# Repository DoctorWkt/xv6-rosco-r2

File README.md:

# xv6-rosco-r2 - xv6 on the Rosco m68k Classic v2

This project aims to port the [xv6](https://github.com/mit-pdos/xv6-public) kernel
to the [Rosco m68k Classic v2](https://github.com/rosco-m68k/rosco_m68k) SBC. The
goal is to have a Unix-like kernel with a BSD userland on top of it, much like my
previous [xv6-freebsd](https://github.com/DoctorWkt/xv6-freebsd) project.

This time, I'm going to do things in a few stages:

 - Stage 1: Bring up a system with just one program running at a time. I've
   done this before with the [Nine-E](https://github.com/DoctorWkt/Nine-E/) project.
 - Stage 2: Move to multiple processes but with no process pre-emption. I've done
   this before with the [MMU09](https://github.com/DoctorWkt/MMU09) project.
 - Stage 3: Enable process pre-emption and then slowly add in all the libraries
   and userland from the [xv6-freebsd](https://github.com/DoctorWkt/xv6-freebsd) project.

Please note: this is a work in progress. It's definitely not a finished and polished
system at the moment. You will have to figure some things out yourself.

## Hardware Options

I'm finding the bit-bang SD card very slow. I also really don't want to have to put
in a relocating loader into the kernel. So I have designed an
[expansion board](hardware) with 1M of RAM and a
[CH375](https://www.electrodragon.com/product/ch375-module-reading-and-writing-u-diskusb-communicate/)
USB interface. It has a
[base register](https://en.wikipedia.org/wiki/Base_and_bounds) in front of the RAM, so that I can have multiple processes, but each one will think that they start at the same base address.

There are two Git branches for this project:

 - This branch, `ch375`, has the code that supports the above expansion board.
   In this version, the system has multiple processes running at any time.
 - The `main` branch has the code that supports the SD card. In that version,
   there is only one program running at any time.

## Running the System in an Emulator

If you want to try this out without the hardware, then build my
[r68k emulator](https://github.com/DoctorWkt/rosco_m68k/tree/wkt_r68k/code/tools/r68k).

In this repository, I have provided a copy of the `xv6` kernel binary: `kern/xv6.bin`, and a filesystem image: `fs.img`. Copy these to where you built the emulator. Now you can do:

```
$ ./r68k -U fs.img xv6.bin
```

and you will see:

```
Welcome to xv6
About to initialise the CH375
xv6 superblock: size 9000 nblocks 8949 ninodes 200
  nlog 20 logstart 2 inodestart 22 bmap start 48
$ ls -l
-rwxrwxrwx     1 root root     46 Wed Sep  4 23:49:10 README
drwxrwxrwx     1 root root    896 Mon Oct 14 21:38:24 bin
drwxrwxrwx     1 root root     64 Wed Sep  4 23:27:09 etc
-rwxrwxrwx     1 root root   6071 Tue Aug  8 01:30:40 roff_manual
$
```

## Building the System for the CH375 Device

I need to put more docs here, but for now ...

You will need the [rosco toolchain](https://rosco-m68k.com/docs/toolchain-installation)
installed on your system as well as `mtools` and `mkfs.vfat`. There are probably a few
more things needed - let me know what I've forgotten.

At the top level, do a `make` to build the kernel, the tools, the libraries and
the commands. This will build the `fs.img` xv6 filesystem image.

Yes, there are a heap of warnings. Over time, I will try to fix them.

Then, do a `make sdcard.img`. This creates the SD card image with a bootable copy
of the `xv6` kernel.

Now write `sdcard.img` to your SD card, write `fs.img` to your USB key, put each
in the correct socket, and boot your rosco board with the CH375 expansion board.

You should see something like:

```
                                 ___ ___ _   
 ___ ___ ___ ___ ___       _____|  _| . | |_ 
|  _| . |_ -|  _| . |     |     | . | . | '_|
|_| |___|___|___|___|_____|_|_|_|___|___|_,_|
                    |_____|      Classic 2.42

MC68010 CPU @ 10.0MHz with 14680064 bytes RAM
Initializing hard drives... No IDE interface found
Searching for boot media...
SD v2 card:
  Partition 1: Loading "/ROSCODE1.BIN"....
Loaded 16600 bytes in ~1 sec.

Welcome to xv6
About to initialise the CH375
xv6 superblock: size 9000 nblocks 8949 ninodes 200
  nlog 20 logstart 2 inodestart 22 bmap start 48
$ setdate
Enter new date (yyyy-mm-dd): 2024-10-14
Enter new time (hh:mm:ss): 11:07:00
New time is Mon Oct 14 11:07:00 2024

$ touch README
$ ls -l
-rwxrwxrwx     1 root root     46 Mon Oct 14 11:07:05 README
-rwxrwxrwx     1 root root  42497 Thu Jan  1 00:01:13 bar
drwxrwxrwx     1 root root    896 Mon Oct 14 00:49:48 bin
drwxrwxrwx     1 root root     64 Wed Sep  4 23:27:09 etc
-rwxrwxrwx     1 root root  42497 Thu Jan  1 00:00:43 foo
-rwxrwxrwx     1 root root   6071 Tue Aug  8 01:30:40 roff_manual
$
```

## Status -- 29 Oct 2024

I've decided to replace the BSD libraries and commands with
the libraries and commands from Minix. There are now a lot 
more commands, and the libraries are smaller too.

## Status -- 22 Oct 2024

I've added double-indirect blocks to the filesystem. Files can
now be up to 32 Megabytes in size.

## Status - 21 Oct 2024

I've imported some assembly language versions of `memmove()` and `memset()`.
I've also rewritten some of the loops in the `balloc()` block allocation
function. All of this has greatly improved the file I/O speed, especially
writes to disk.

## Status - 17 Oct 2024

I found a workaround for the problem with the `vi` editor writing files really
slowly, but I haven't found the underlying bug yet.

**BIG CHANGE**: I modified the disk block buffer to _not_ write out dirty blocks,
and added the `sync` program and `sync()` system call to flush out dirty blocks.
This improves disk performance, but you must remember to `sync` before turning off
the system now!

## Status - 15 Oct 2024

The PCBs have arrived and the CH375 device works fine. While waiting for the PCBs,
I got `fork()`, `exit()` and `wait()` working correctly in the emulator. They also
work in hardware with the memory on the PCB.

There is now an `init` process, and I've imported the `xv6` shell. So now the system
has working processes. Pipes are also working, so you can now do:

```
$ roff roff_manual | less
```

## Status - 5 Oct 2024

I have started the work in the `ch375` branch to add processes to the system.
There is still only one process, but I've brought back the `proc` structure
and I've begun the work to write the memory management code.

## Status - 1 Oct 2024

I've imported the KiCad design for my expansion RAM + base register + CH375 board
and done a bit of documentation on it. I've ordered PCBs and I'm waiting for them
to arrive so I can test if the board works.

## Status - 24 Sept 2024

I've imported a bunch more commands, this time from FUZIX.
I also got the kernel to return an `errno` value back to
userland.

## Status - 19 Sept 2024

I've imported more programs, replaced `malloc()` with the Minix version and
added `readline()` support to the shell.

## Status - 17 Sept 2024

I have stage 1 up and running on the
[Rosco m68k Classic v2](https://github.com/rosco-m68k/rosco_m68k) SBC with the
bit-bang SD card. There are only a few programs in the userland at present:
`cal`, `cat`, `echo`, `ls`, `rm`, `sh`.

The kernel has these system calls:
`exit()`, `read()`, `write()`, `open()`, `close()`, `link()`, `unlink()`, `chdir()`,
`fstat()`, `dup()`, `mkdir()`, `spawn()`, `lseek()`, `time()`, `ioctl()`.

As there are no processes, `spawn()` acts like the Unix `exec()` and replaces the
current program, and `exit()` simply `spawn()s` the shell.

The next steps are to port more programs over from
[xv6-freebsd](https://github.com/DoctorWkt/xv6-freebsd) and
[Nine-E](https://github.com/DoctorWkt/Nine-E/).

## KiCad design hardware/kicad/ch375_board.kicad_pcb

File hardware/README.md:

## RAM Expansion and CH375 Board for Rosco Classic v2

The 680000 doesn't have any built-in memory management, and I didn't want
to write the code to load and relocate an ELF binary so that it could run
at any specific base memory address. I also wanted to support the
[CH375](https://www.electrodragon.com/product/ch375-module-reading-and-writing-u-diskusb-communicate/)
device, which provides an 8-bit parallel interface to USB block devices.

Thus, I have built an expansion card that `xv6` uses. It has two main
components:

 - the CH375 device and associated addressing/interrupt components
 - 1M of expansion RAM along with primitive memory management hardware

In this directory you can find the [KiCad board design](kicad), the
[code](pld) for the two GALs on the board, a PDF of the
[schematic](schematic.pdf), a mock-up [image](ch375_board.jpg)
of the board and some [documentation](docs) on the CH375 device.

## The CH375 Device

The CH375 provides block-level access to a USB via an 8-bit TTL-compatible
parallel interface. We need to decode two I/O addresses for this device.
We also need to convert the active-low interrupt that the CH375 generates
into several lines that make it compatible with the 68000 auto-vector
interrupt protocol.

The [GAL code](pld/ch375logic.pld) that interfaces between the 68000 and the
CH375 does these things:

 - It sets the CH375 chip select low for addresses $00FFF001 (data) and
   $00FFF003 (commands), and lowers DTACK at the same time.
 - After the CH375 sends an interrupt, the CPU responds with various lines
   to acknowledge the interrupt. The GAL determines when to drop VPA to
   let the CPU know that the interrupt has been acknowledged.

## The Expansion RAM and the Base Register

The expansion board adds 1M of expansion RAM to the Rosco classic r2 board.
It also provides primitive memory management hardware in the form of a
[base register](https://en.wikipedia.org/wiki/Base_and_bounds). Let's look
at how this works.

The base register is a 4-bit I/O register (initially zero) which can be written
to at address $00FFE001.

The base register's value, multiplied by 64K, is then added to any expansion
RAM address. This allows the "base" of the expansion RAM to be positioned
at any of sixteen 64K-spaced locations.

For example, with the base register set to 0x0, expansion memory address
$00100124 becomes $00100124 + $0000000 => $00100124. But if the base
register was set to 0x4, then address $00100124 becomes
$00100124 + $0040000 => $00140124.

The purpose of the base register is to allow an operating system to load
multiple programs into the expansion RAM, each starting at a different
64K position. By setting the base register suitably, each program will
think that it starts at $00100000 instead of its actual physical location.

In terms of hardware, the register itself is a 74HCT161 4-bit register, and the
[GAL code](pld/ramdecode.pld) in the second GAL decodes its $00FFE001 address.
This is connected to a 74HCT283 4-bit adder. The base register's value is added
to address lines A16...A19 to form the physical address that is then sent to the
two RAM chips.

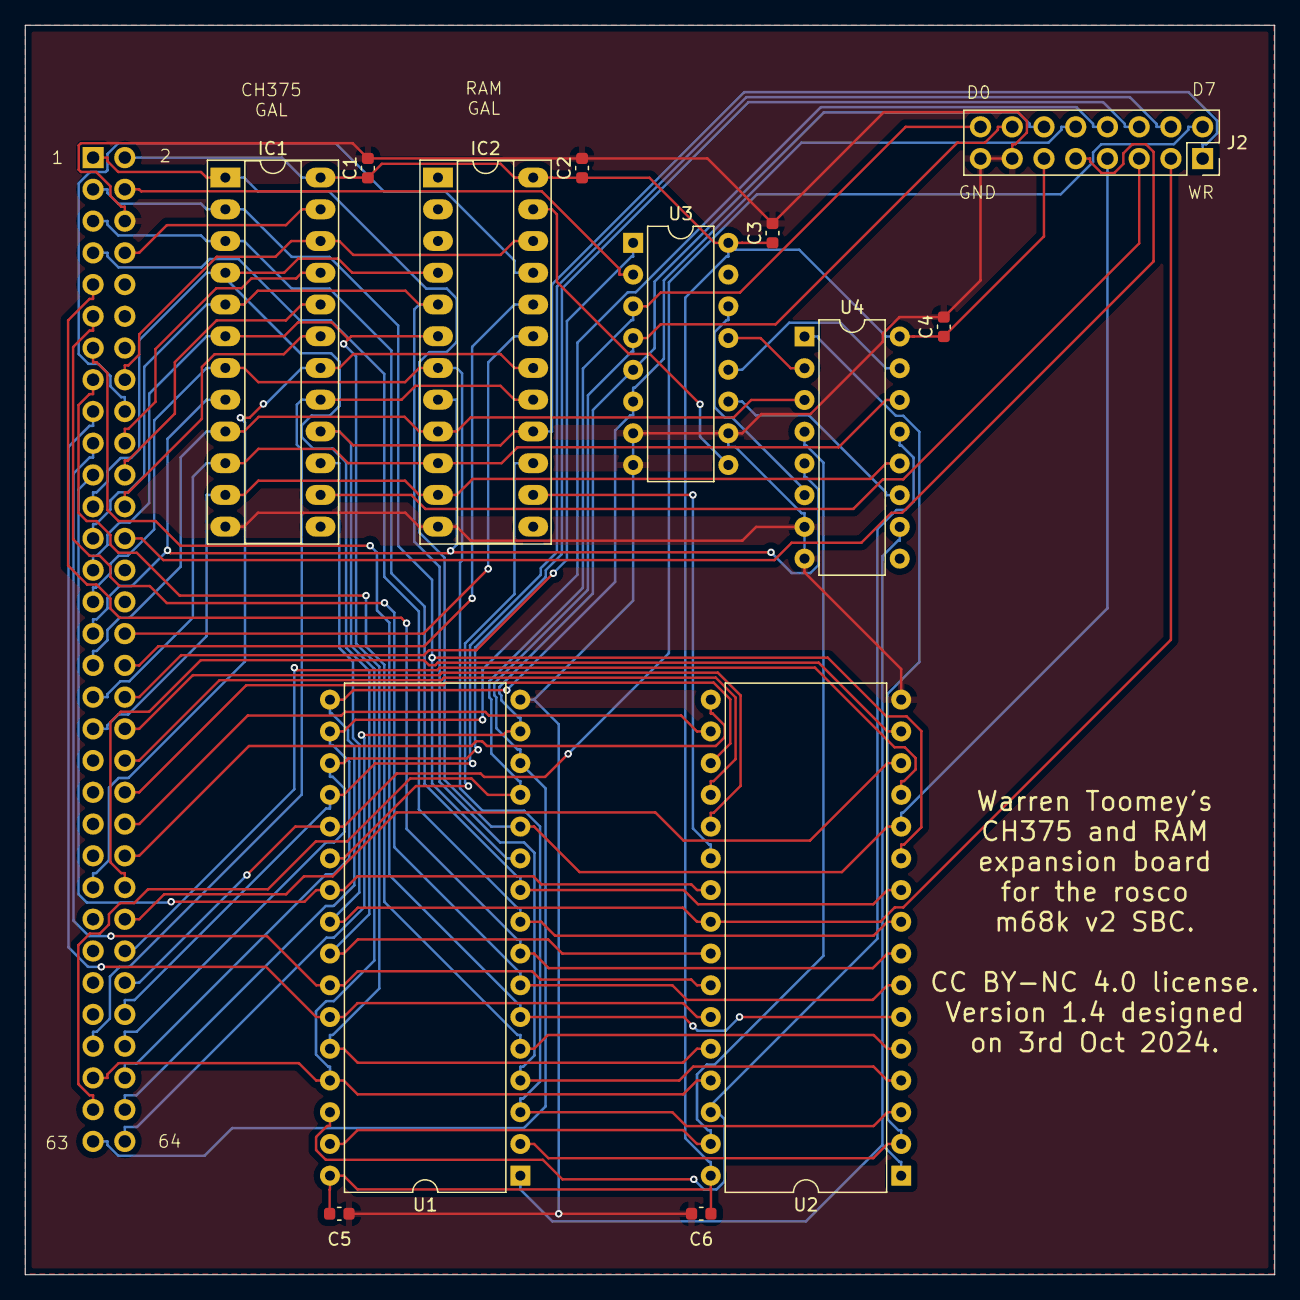
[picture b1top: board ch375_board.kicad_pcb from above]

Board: 2 copper layers, 100.0 x 100.0 mm, 14 parts (1 on the bottom side), 64 nets.

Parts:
C1, C2, C3, C4, C5, C6: 100nF; C_0603_1608Metric
IC1, IC2: ATF22V10C; DIP-24_W7.62mm_Socket_LongPads
J1: Conn_02x32_Odd_Even; PinSocket_2x32_P2.54mm_Vertical
J2: Conn_02x08_Odd_Even; PinSocket_2x08_P2.54mm_Vertical
U1, U2: AS6C4008-55PCN; DIP-32_W15.24mm
U3: 74HCT161; DIP-16_W7.62mm
U4: 74LS283; DIP-16_W7.62mm

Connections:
A1: IC1.1 (I1/CLK), J1.1, J2.7, U1.12 (A0), U2.12 (A0)
A2: IC1.2 (I2), J1.3, U1.11 (A1), U2.11 (A1)
A3: IC1.3 (I3), J1.5, U1.10 (A2), U2.10 (A2)
A4: J1.7, U1.9 (A3), U2.9 (A3)
A5: J1.9, U1.8 (A4), U2.8 (A4)
A6: J1.11, U1.7 (A5), U2.7 (A5)
A7: J1.13, U1.6 (A6), U2.6 (A6)
A8: J1.15, U1.5 (A7), U2.5 (A7)
A9: J1.17, U1.27 (A8), U2.27 (A8)
A10: J1.19, U1.26 (A9), U2.26 (A9)
A11: J1.21, U1.23 (A10), U2.23 (A10)
A12: IC1.4 (I4/PD), IC2.4 (I4/PD), J1.23, U1.25 (A11), U2.25 (A11)
A13: IC1.5 (I5), IC2.5 (I5), J1.25, U1.4 (A12), U2.4 (A12)
A14: IC1.6 (I6), IC2.6 (I6), J1.27, U1.28 (A13), U2.28 (A13)
A15: IC1.7 (I7), IC2.7 (I7), J1.29, U1.3 (A14), U2.3 (A14)
A16: IC1.8 (I8), IC2.8 (I8), J1.31, U4.5 (A1)
A17: IC1.9 (I9), IC2.9 (I9), J1.33, U4.3 (A2)
A18: IC1.10 (I10), IC2.10 (I10), J1.35, U4.14 (A3)
A19: IC1.11 (I11), IC2.11 (I11), J1.37, U4.12 (A4)
AS: IC1.18 (IO5), IC2.18 (IO5), J1.47
CLK: J1.4, U3.2 (CP)
D0: J1.61, J2.16, U1.13 (DQ0), U3.3 (D0)
D1: J1.63, J2.14, U1.14 (DQ1), U3.4 (D1)
D2: J1.64, J2.12, U1.15 (DQ2), U3.5 (D2)
D3: J1.62, J2.10, U1.17 (DQ3), U3.6 (D3)
D4: J1.60, J2.8, U1.18 (DQ4)
D5: J1.58, J2.6, U1.19 (DQ5)
D6: J1.56, J2.4, U1.20 (DQ6)
D7: J1.54, J2.2, U1.21 (DQ7)
D8: J1.52, U2.13 (DQ0)
D9: J1.50, U2.14 (DQ1)
D10: J1.48, U2.15 (DQ2)
D11: J1.46, U2.17 (DQ3)
D12: J1.44, U2.18 (DQ4)
D13: J1.42, U2.19 (DQ5)
D14: J1.40, U2.20 (DQ6)
D15: J1.38, U2.21 (DQ7)
DTACK: IC1.17 (I04), IC2.17 (I04), J1.57
EXPSEL: IC2.21 (IO8), J1.18
FC0: IC1.21 (IO8), J1.20
FC1: IC1.20 (IO7), J1.22
FC2: IC1.19 (IO6), J1.24
GND: C1.2, C2.2, C3.2, C4.2, C5.2, C6.2, IC1.12 (GND), IC2.12 (GND), J1.6, J2.13, J2.15, U1.16 (VSS), U2.16 (VSS), U3.7 (CEP), U3.8 (GND), U3.10 (CET), U4.7 (C0), U4.8 (GND)
IOSEL: IC1.22 (IO9), IC2.22 (IO9), J1.16
IRQ5: J1.26, J2.9
LDS: IC2.19 (IO6), J1.32
unnamed: U3.14 (Q0), U4.6 (B1)
unnamed: U3.13 (Q1), U4.2 (B2)
unnamed: U3.12 (Q2), U4.15 (B3)
unnamed: U3.11 (Q3), U4.11 (B4)
P16: U1.31 (A15), U2.31 (A15), U4.4 (S1)
P17: U1.2 (A16), U2.2 (A16), U4.1 (S2)
P18: U1.30 (A17), U2.30 (A17), U4.13 (S3)
P19: U1.1 (A18), U2.1 (A18), U4.10 (S4)
RESET: J1.36, U3.1 (~MR)
R~W: IC1.16 (IO3), IC2.16 (IO3), J1.59, J2.1, U1.29 (WE#), U2.29 (WE#)
UDS: IC2.20 (IO7), J1.34
VCC: C1.1, C2.1, C3.1, C4.1, C5.1, C6.1, IC1.24 (VCC), IC2.24 (VCC), J1.2, J2.11, U1.32 (VCC), U2.32 (VCC), U3.16 (VCC), U4.16 (VCC)
VPA: IC1.23 (IO10), J1.8
W~R: IC1.15 (IO2), J2.3, U1.24 (OE#), U2.24 (OE#)
~BASESEL: IC2.23 (IO10), U3.9 (~PE)
~CHCS: IC1.14 (IO1), J2.5
~ERAM1: IC2.14 (IO1), U2.22 (CE#)
~ORAM1: IC2.15 (IO2), U1.22 (CE#)

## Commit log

2024-09-16 Initial import from my local repo.
2024-09-16 README.md: fix a typo.
2024-09-16 Makefile: ensure the `build` directory gets created.
2024-09-17 spawn.c: Fix typo in comment.
2024-09-17 cmds/simple: Imported more commands from the MMU09 project.
2024-09-17 Added cp and less commands, added creat(), fixed the duplicate __atexit.
2024-09-17 cmds/simple/sh.c: Got pipes to work.
2024-09-17 sd-img.zip: Updated the SD image with cp, less and the shell with pipelines.
2024-09-19 malloc.c: The FreeBSD version seemed to cause address errors. I've imported the Minix version as a replacement.
2024-09-19 sd-img.zip: Updated with the Minix malloc library function.
2024-09-19 sh: I imported a readline library so it can be used in the shell.
2024-09-19 sd-img.zip: Updated the shell binary with the readline library.
2024-09-19 README.md: Updated the status section.
2024-09-19 readline.c: Actually add it to the repo.
2024-09-19 cmds/s: The s editor is a cut-down vi clone.
2024-09-19 sd-img.zip: Added the binary of the s (vi) editor.
2024-09-22 kern/clock.c: Added the time() and stime() system calls, and userland programs to see the date/time and set the date/time.
2024-09-22 cmds/simple/Makefile: Add this too!
2024-09-22 cmds/s/Makefile: Clean up the map file.
2024-09-22 sd-img.zip: Added the new date executables.
2024-09-22 kern/clock.c: Added the sleep() system call.
2024-09-22 cmds/simple/sleep.c: Userland program
2024-09-22 kernel: Replace CR with LF on input lines. shell: Don't print a spurious blank line after each command input.
2024-09-24 cmds/simple: Several more commands imported from FUZIX.
2024-09-24 sd-img.zip: Updated to have the new commands from FUZIX.
2024-09-24 kern/sysfile.c: The kernel now returns an errno value back to userland.
2024-09-25 grep.c: Replaced with the one from 4.3BSD.
2024-09-25 kern/sysfile.c: Added the fchdir() syscall.
2024-09-25 include/xv6/fs.h: The on-disk inodes now have an mtime field. More to come!
2024-09-25 kern.fs.c: Added the code to read/write mtime fields.
2024-09-25 lib/sys/stat.c: Make the kernel mtimes visible to the userland.
2024-09-25 cmds/simple: Added a few more commands from FreeBSD.
2024-09-25 cmds/simple/du.c: Imported, but crashes with a malloc error :-(
2024-09-25 cmds/simple/Makefile: This too!
2024-09-28 kern/asmcode.s: I forgot that I had to turn off the interrupt before exiting the interrupt handler!
2024-09-28 sd-img.zip: Updated this with the kernel patch to the tick interrupt handler.
2024-09-28 kern/sysfile.c: Added the utime() syscall and imported the touch command.
2024-09-28 Added the touch command, and got the CH375 block code to work with the 100Hz timer running.
2024-09-28 kern/Makefile: Changed it back to use the SD card for now.
2024-10-01 hardware: I've added the `hardware` directory which has my expansion board design.
2024-10-01 hardware/README.md: typos
2024-10-01 README.md: updated the status.
2024-10-03 hardware: Updated the PCB design now that I actually understand how to do autovector interrupts!
2024-10-03 hardware/pld: Updated the GAL logic files to match the new PCB.
2024-10-03 hardware/README.md: Updated with details of the new GAL logic code.
2024-10-03 kern: I changed the code to use IRQ5 instead of IRQ3.
2024-10-03 lib/sys/crt0.s: Added an "a.out" header which we will use later when we have processes.
2024-10-03 misc/userland_program.ld: Moved the start address of programs to the base of the expansion RAM.
2024-10-03 kern/spawn.c: Modified spawn() to check the a.out header in an executable.
2024-10-04 kern/spinlock.c: I've introduced the spinlock functions but not used them yet.
2024-10-04 kern/Makefile: oops, turned on SD card by mistake!
2024-10-04 kern: I've added the spinlock acquire() and release() code back into the relevant kernel files. They seem to work so far.
2024-10-04 kern/proc.c: I've made a start on adding the proc code. It's unused as yet.
2024-10-04 kern: I've removed the spinlocks as they are causing an infinite loop. Given we have only one CPU, we don't really need them.
2024-10-04 kern: I've moved the process working directory into a process table entry instead of being a single variable.
2024-10-04 cmds/simple/chmem.c: A quick program to change a program's required memory.
2024-10-04 cmds/simple/size.c: A program to see the size of an executable's sections.
2024-10-04 various: Added the data size to the a.out header. Added the beginnings of frame code (VM) to the kernel, but not using it just yet.
2024-10-04 lib.sys: Now that sleep() defined in the kernel, a few modifications to prevent conflict with the userland sleep() definition.
2024-10-05 kern: I've brought back the global `proc` pointer in preparation for moving file descriptors back to being per-process.
2024-10-05 kern/sysfile.c: File descriptors are now per-process!
2024-10-05 various: I've renamed spawn() to be exec() as that is what it will become.
2024-10-05 kern/exec.c: Renamed spawn.c to exec.c
2024-10-05 kern/spawn.c: Deleted.
2024-10-05 tools/chmem.c: Added this so we can change the memory on binaries before we install them in the filesystem image.
2024-10-05 kern/exec.c: We now copy arguments down to the kernel, have frames allocated, and set the base register before copying arguments up to the new program's memory. There are some bugs to fix!
2024-10-05 kern/exec.c: Get exit() to release a program's allocated memory.
2024-10-05 various: Remove old RCS tags.
2024-10-05 kern/exec.c: I reworked this to ensure we can cleanly move to the new program's stack.
2024-10-05 cmds: Mark some programs as needing more than 64K of RAM.
2024-10-06 kern/proc.c: I've made a start on the context switch code and the process scheduler. Still a work in progress.
2024-10-06 kern/proc.c: I added the code for wait() but not tested yet.
2024-10-06 kern/proc.c: I've done most of the fork() code. Copying memory from the parent to the child will be interesting, as we will need to set the base register to 0 so we can see both of them, which will s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
2024-10-06 kern/proc.c: I moved sbrk() and brk() into the kernel. We can use the current brk value to minimise how much memory fork() has to copy.
2024-10-06 kern/proc.c: We have a sort-of working fork(). No scheduling yet. The fork() creates a new process and copies the memory. But I don't know if I can swtch() over to it yet.
2024-10-07 kern/proc.c: fork() seems to work. Very painful to get here!
2024-10-10 kern/proc.c: I think I finally have wait() working. We can fork(), get the parent to block, let the child run and exit. Then, wakeup the parent, get the child's status and return to userland. Yay!
2024-10-10 kern/proc.c: Free an exiting process' memory sooner than later.
2024-10-10 cmds/simple/init.c: I've imported init, but can't start the 1st child yet.
2024-10-12 kern/proc.c: I finally have fork(), exec(), exit() and wait() working. I had to put the process context into the proc structure as it was too hard trying to leave it on the stack.
2024-10-12 kern/asmcode.s, kern/proc.c: Tidied up the code.
2024-10-13 lib/sys/syscalls.s: Prepare the way for pipe().
2024-10-13 kern/asmcode.s: Don't start the timer as it already is running.
2024-10-13 README.md: Brought the status up to date.
2024-10-13 kern/asmcode.s: Get the UART IMR address correct.
2024-10-13 kern/asmcode.s: Get the correct UART IMR address.
2024-10-13 cmds/simple/sh.c: Import of the xv6 shell with readline modifications. We now have a working system with fork/exec/exit/wait. So good!
2024-10-14 kern/pipe.c: I've added the pipe() code, not working yet.
2024-10-14 cmds/simple/sh.c: Fixed some input bugs in the shell, and fixed cd.
2024-10-14 include/xv6/param.h: Tried to improve I/O speed with more buffers, no change :-(
2024-10-14 README.md: I changed the ch375 version to reflect the new hardware.
2024-10-14 kern/usbblk.c: I rewrote the USB read/write code in assembly for speed.
2024-10-14 kern/asmcode.s: I unrolled the read/write inner loops to improve speed. I'm now getting a 50% speed improvement over the old code.
2024-10-14 I added copies of the xv6 executable and the filesystem image. This lets people play with the system using my r68k emulator.
2024-10-15 kern/asmcode.s: I forgot to update the sydcall table with sys_pipe. Fixed.
2024-10-15 README.md: Updated to mention that pipes work.
2024-10-15 I added a CR -> NL input flag which can be set by tcsetattr(). This fixes vi.
2024-10-16 kern/proc.c: Added the getpid() system call.
2024-10-17 cmds/s/commands.c: I worked around the file writing bug in the editor. What's happening is that, sometimes, `fprintf()` ends up writing single bytes using `write()`. I have no idea why. But if we use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
2024-10-17 kern/bio.c: BEWARE! Dirty disk blocks now not written to disk. Use `sync` to do this !!!!
2024-10-17 README.md: Update status, warn people about needing to `sync` now!
2024-10-19 kern/memmove.s: Import of memmove() from NetBSD to improve disk I/O.
2024-10-19 kern/memset.s: Imported memset() from NetBSD to improve disk I/O performance.
2024-10-20 kern/fs.c: Improved the disk I/O performance with balloc() rewrite.
2024-10-20 kern/fs.c: Another `balloc()` change, disk writes now much faster! Rather than starting at the beginning of each bitmap block, we now start at the index position we last allocated from. The chances o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
2024-10-22 Trying to get double indirect blocks to work. Not yet!
2024-10-22 kern/fs.c: I got doubly-indirect blocks working, yay!
2024-10-22 README.md: Updated with a note about large files.
2024-10-23 cmds/s/commands.c: Improve speed of editor saving.
2024-10-23 kern/fs.c: Speed up allocation of new blocks.
2024-10-23 kern: Replaced C version of memset() and memmove() with asm one for speed.
2024-10-23 kern: Added the CR -> NL translation code to the kernel.
2024-10-24 I added the code to allow dirty disk blocks to stay in memory + the sync command.
2024-10-24 kern/fs.c: Added double indirect blocks, files can now be up to 32M in size.
2024-10-24 I increased the size of the disk cache and moved the programs' base address to match. This makes it all a bit faster as most disk writes stay in memory until a `sync`.
2024-10-24 Removed RCS strings from the files.
2024-10-25 Makefiles: use the m68k-elf-ranlib instead of the native ranlib.
2024-10-25 Makefile: do the same with `ar` that I just did with `ranlib`.
2024-10-28 tools/mkfs.c: Allow more than 4,096 used disk blocks :-)
2024-10-28 The first big import of Minix libs and commands.
2024-10-28 LICENSE: Update with details about the Minix files.
2024-10-28 LICENSE.Minix: Added this file.
2024-10-28 I fixed a few things to allow make clean; make to work.
2024-10-28 README.md: Update the status with the Minix change.
2024-10-28 I renamed LICENSE.minix to match the other licenses.
2024-10-29 include/fcntl.h: Fixed flags to match the xv6 kernel.
2024-10-29 cmds/simple/rm.c: Brought back the old version.
2024-10-29 tools/mkfs.c: I fixed a really dumb bug in balloc().
2024-10-29 fs.img: Built with the fixed `mkfs`.
2024-10-29 cmds/simple/mv.c: Brought the old version back.
2024-10-30 cmds/simple/ttt.c: Fix up the drawing of the first board.
2024-10-30 kern/console.c: Code rearranged in preparation for input line editing.
2024-10-30 kern/console.c: Added line editing to the console.
2024-10-30 cmds/nroff: I got nroff to work!
2024-10-30 fs_skel/usr: I started adding the usual stuff in /usr.
2024-10-30 We can now build `man` but it doesn't work yet.
2024-11-01 tools/mkfs.c: More inodes
2024-11-01 lib/sys/Makefile: Added waitpid
2024-11-01 cmds/simple/man.c: I added a new man program and imported some man pages. I need to curate the actual man pages a bit.
2024-11-01 mans: I did a bit of curating with the manuals.
2024-11-02 Moved a few documents around and updated the README.

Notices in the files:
hardware/kicad/ch375_board.kicad_pcb:
CC BY-NC 4.0 license.
